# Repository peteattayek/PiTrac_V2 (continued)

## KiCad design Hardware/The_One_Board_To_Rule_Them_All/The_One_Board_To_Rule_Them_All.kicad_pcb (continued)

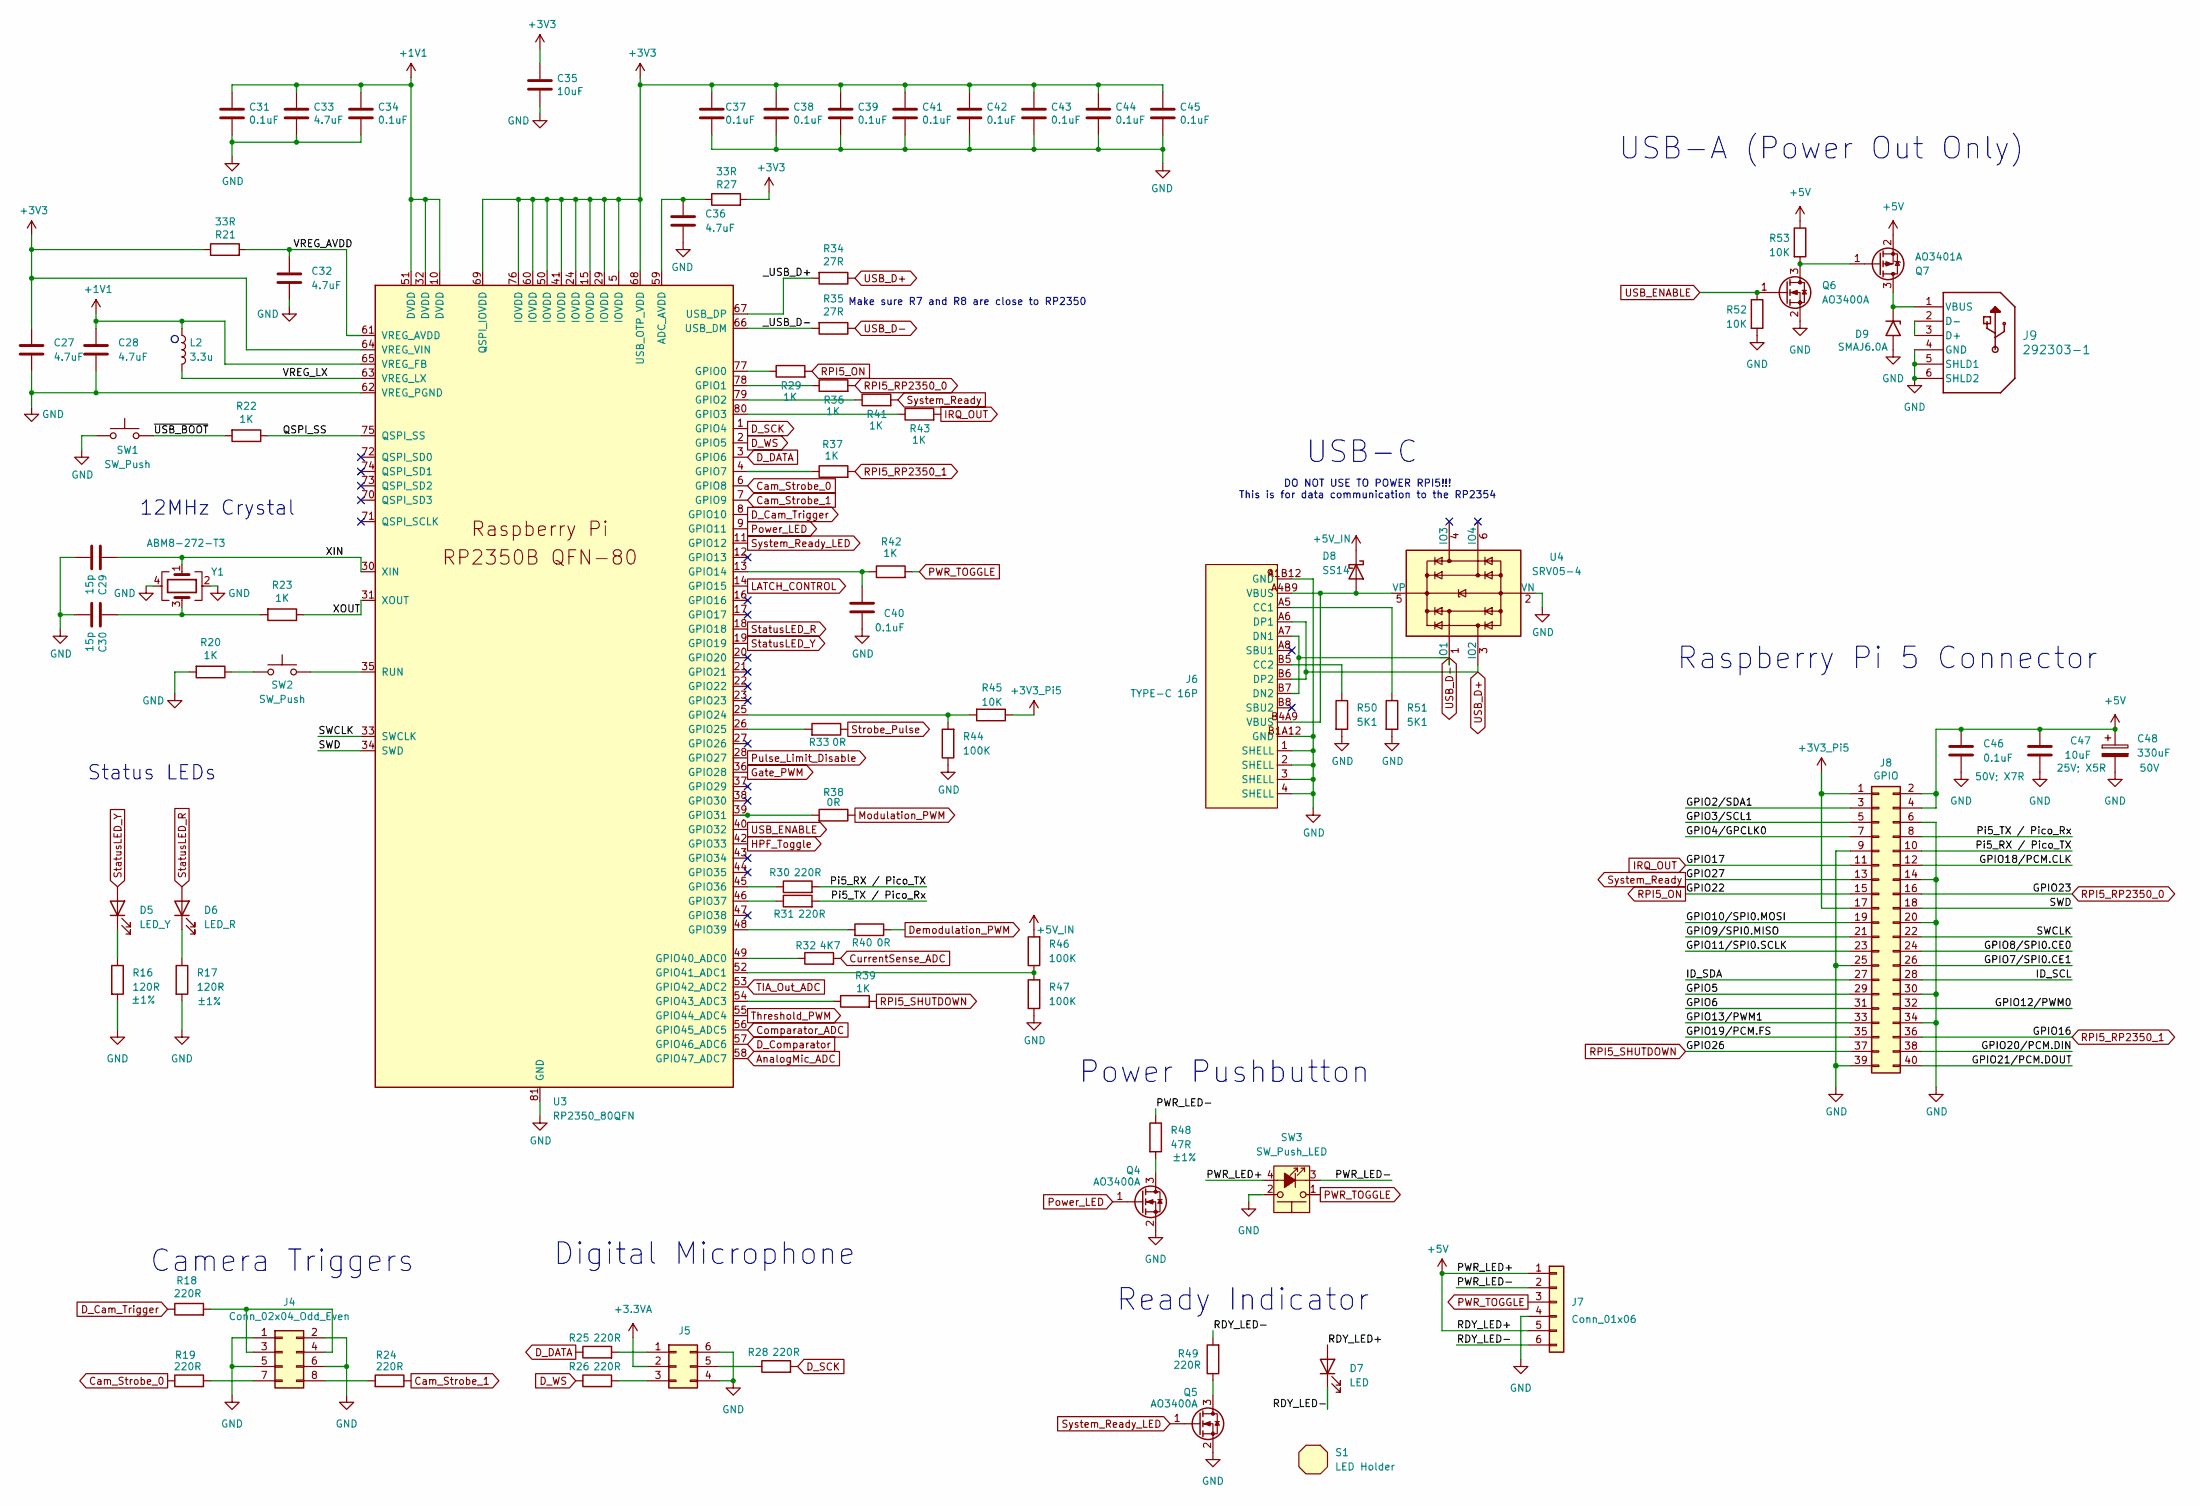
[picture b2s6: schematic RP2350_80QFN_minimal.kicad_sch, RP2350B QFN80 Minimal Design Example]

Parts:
C27, C28: 4.7uF; C_0402_1005Metric_small_pads; Ratings 10V; X5R; MPN CL05A475MP5NRNC; LCSC C23733
C29, C30: 15p; C_0402_1005Metric; Ratings C0G; MPN GRM1555C1H150JA01D; LCSC C1548
C31, C34, C37, C38, C39, C40, C41, C42, C43, C44, C45, C46: 0.1uF; C_0402_1005Metric; Ratings 50V; X7R; MPN CL05B104KB54PNC; LCSC C307331
C32, C33, C36: 4.7uF; C_0402_1005Metric; Ratings 10V; X5R; MPN CL05A475MP5NRNC; LCSC C23733
C35, C47: 10uF; C_0603_1608Metric; Ratings 25V; X5R; MPN CL10A106MA8NRNC; LCSC C96446
C48: 330uF; CAP_50TPV_10x10.5_RBY; Ratings 50V; MPN 50TPV330M10X10.5; LCSC C53120968
D5: LED_Y; LED_0603_1608Metric; MPN APT1608SYCK; LCSC C89811
D6: LED_R; LED_0603_1608Metric; MPN AA1608SURSK; LCSC C2286
D7: LED; MPN BL-BGE1V1
D8: SS14; D_SMA; MPN SS14; LCSC C2480
D9: SMAJ6.0A; D_SMA; MPN SMAJ6.0A; LCSC C19077525
J4: Conn_02x04_Odd_Even; PinHeader_2x04_P2.54mm_Vertical; MPN PH2-08-UA
J5: Conn_02x03_Counter_Clockwise; PinHeader_2x03_P2.54mm_Vertical; MPN PH2-06-UA
J6: TYPE-C 16P; USB-C-SMD_TYPE-C16PIN_C668624; MPN USB4105-GF-A; LCSC Part C668624
J7: Conn_01x06; PinHeader_1x06_P2.54mm_Vertical; MPN PH1-06-UA
J8: GPIO; PinSocket_2x20_P2.54mm_Vertical; MPN 16764
J9: 292303-1; CONN4_292303-1_TEC; MPN 292303-1
L2: 3.3u; L_pol_2016; MPN AOTA-B201610S3R3-101-T; LCSC C42411119
Q4, Q5: AO3400A; SOT-23; MPN AO3400A; LCSC C20917
Q6: AO3400A; SOT-23; MPN AO3400A; Digikey PN 785-1000-1-ND
Q7: AO3401A; SOT-23; MPN AO3401A; LCSC C15127
R16, R17: 120R; R_0402_1005Metric; Ratings ±1%; MPN RMCF0402FT120R; LCSC C25079
R18, R19, R24, R25, R26, R28, R30, R31, R49: 220R; R_0402_1005Metric; Ratings ±1%; MPN RMCF0402FT220R; LCSC C25091
R20, R22, R23, R29, R36, R37, R39, R41, R42, R43: 1K; R_0402_1005Metric; Ratings ±1%; MPN RMCF0402FT1K00; LCSC C11702
R21, R27: 33R; R_0402_1005Metric; Ratings ±1%; MPN RMCF0402FT33R0; LCSC C25105
R32: 4K7; R_1206_3216Metric; Ratings ±1% 1/4W; MPN RMCF1206FT4K70; LCSC C17936
R33, R38, R40: 0R; R_0805_2012Metric_Pad1.20x1.40mm_HandSolder; MPN RMCF0805ZT0R00; LCSC C17477
R34, R35: 27R; R_0603_1608Metric; Ratings ±1%; MPN RMCF0603FT27R0; LCSC C25190
R44, R46, R47: 100K; R_0402_1005Metric; Ratings ±1%; MPN RMCF0402FT100K; LCSC C25741
R45, R52, R53: 10K; R_0402_1005Metric; Ratings ±1%; MPN RMCF0402FT10K0; LCSC C25744
R48: 47R; R_0402_1005Metric; Ratings ±1%; MPN RMCF0402FT47R0; LCSC C25118
R50, R51: 5K1; R_0402_1005Metric; Ratings ±1%; MPN RMCF0402FT5K10; LCSC C25905
S1: LED Holder; MPN SSH-LXH501
SW1, SW2: SW_Push; SW_TS-1088_XNP; MPN TS-1088-AR02016; LCSC C720477
SW3: SW_Push_LED; MPN 481
U3: RP2350_80QFN; RP2350-QFN-80-1EP_10x10_P0.4mm_EP3.4x3.4mm_ThermalVias; MPN RP2354B; LCSC C39843328
U4: SRV05-4; SOT-23-6; MPN SRV05-4HTG-D; LCSC C7420376
Y1: ABM8-272-T3; Crystal_SMD_3225-4Pin_3.2x2.5mm; MPN ABM8-272-T3; LCSC C20625731

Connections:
+1V1: C28.1, C31.1, C33.1, C34.1, L2.1, U3.10 (DVDD), U3.32 (DVDD), U3.51 (DVDD), U3.65 (VREG_FB)
+3.3VA: J5.2; also elsewhere on the board
+3V3: C27.1, C35.1, C37.1, C38.1, C39.1, C41.1, C42.1, C43.1, C44.1, C45.1, R21.1, R27.2, U3.5 (IOVDD), U3.15 (IOVDD), U3.24 (IOVDD), U3.29 (IOVDD), U3.41 (IOVDD), U3.50 (IOVDD), U3.60 (IOVDD), U3.64 (VREG_VIN), U3.68 (USB_OTP_VDD), U3.69 (QSPI_IOVDD), U3.76 (IOVDD); also elsewhere on the board
+3V3_Pi5: J8.1, J8.17, R45.1
+5V: C46.2, C47.1, C48.1, D7.2 (A), J7.1, J7.5, J8.2, J8.4, Q7.2 (S), R53.1, SW3.4 (A); also elsewhere on the board
+5V_IN: D8.1 (K), R46.2; also elsewhere on the board
/MCU and Connectors/GPIO2/SDA1: J8.3
/MCU and Connectors/GPIO3/SCL1: J8.5
/MCU and Connectors/GPIO4/GPCLK0: J8.7
/MCU and Connectors/GPIO5: J8.29
/MCU and Connectors/GPIO6: J8.31
/MCU and Connectors/GPIO7/SPI0.CE1: J8.26
/MCU and Connectors/GPIO8/SPI0.CE0: J8.24
/MCU and Connectors/GPIO9/SPI0.MISO: J8.21
/MCU and Connectors/GPIO10/SPI0.MOSI: J8.19
/MCU and Connectors/GPIO11/SPI0.SCLK: J8.23
/MCU and Connectors/GPIO12/PWM0: J8.32
/MCU and Connectors/GPIO13/PWM1: J8.33
/MCU and Connectors/GPIO18/PCM.CLK: J8.12
/MCU and Connectors/GPIO19/PCM.FS: J8.35
/MCU and Connectors/GPIO20/PCM.DIN: J8.38
/MCU and Connectors/GPIO21/PCM.DOUT: J8.40
/MCU and Connectors/ID_SCL: J8.28
/MCU and Connectors/ID_SDA: J8.27
/MCU and Connectors/PWR_LED-: J7.2, R48.1, SW3.3 (K)
/MCU and Connectors/Pi5_RX / Pico_TX: J8.10, R30.2
/MCU and Connectors/Pi5_TX / Pico_Rx: J8.8, R31.2
/MCU and Connectors/QSPI_SS: R22.1, U3.75 (QSPI_SS)
/MCU and Connectors/RDY_LED-: D7.1 (K), J7.6, R49.2
/MCU and Connectors/SWCLK: J8.22, U3.33 (SWCLK)
/MCU and Connectors/SWD: J8.18, U3.34 (SWD)
/MCU and Connectors/VREG_AVDD: C32.1, R21.2, U3.61 (VREG_AVDD)
/MCU and Connectors/VREG_LX: L2.2, U3.63 (VREG_LX)
/MCU and Connectors/XIN: C29.1, U3.30 (XIN), Y1.1
/MCU and Connectors/XOUT: R23.1, U3.31 (XOUT)
/MCU and Connectors/_USB_D+: R34.2, U3.67 (USB_DP)
/MCU and Connectors/_USB_D-: R35.2, U3.66 (USB_DM)
/MCU and Connectors/~USB_BOOT: R22.2, SW1.2
AnalogMic_ADC: U3.58 (GPIO47_ADC7); also elsewhere on the board
Cam_Strobe_0: R19.1, U3.6 (GPIO8)
Cam_Strobe_1: R24.1, U3.7 (GPIO9)
Comparator_ADC: U3.56 (GPIO45_ADC5); also elsewhere on the board
CurrentSense_ADC: R32.2; also elsewhere on the board
D_Cam_Trigger: R18.1, U3.8 (GPIO10)
D_Comparator: U3.57 (GPIO46_ADC6); also elsewhere on the board
D_DATA: R25.1, U3.3 (GPIO6)
D_SCK: R28.2, U3.1 (GPIO4)
D_WS: R26.1, U3.2 (GPIO5)
Demodulation_PWM: R40.1; also elsewhere on the board
GND: C27.2, C28.2, C29.2, C30.2, C31.2, C32.2, C33.2, C34.2, C35.2, C36.2, C37.2, C38.2, C39.2, C40.1, C41.2, C42.2, C43.2, C44.2, C45.2, C46.1, C47.2, C48.2, D9.2 (A2), J4.1, J4.2, J4.5, J4.6, J5.4, J5.6, J6.1 (SHELL), J6.2 (SHELL), J6.3 (SHELL), J6.4 (SHELL), J6.A1B12 (GND), J6.B1A12 (GND), J7.4, J8.6, J8.9, J8.14, J8.20, J8.25, J8.30, J8.34, J8.39, J9.4 (GND), J9.5 (SHLD1), J9.6 (SHLD2), Q4.2 (S), Q5.2 (S), Q6.2 (S), R16.2, R17.2, R20.2, R44.1, R47.1, R50.2, R51.2, R52.2, SW1.1, SW3.2, U3.62 (VREG_PGND), U3.81 (GND), U4.2 (VN), Y1.2, Y1.4; also elsewhere on the board
Gate_PWM: U3.36 (GPIO28); also elsewhere on the board
HPF_Toggle: U3.42 (GPIO33); also elsewhere on the board
IRQ_OUT: J8.11, R43.2
LATCH_CONTROL: U3.14 (GPIO15); also elsewhere on the board
Modulation_PWM: R38.1; also elsewhere on the board
unnamed: C30.1, R23.2, Y1.3
unnamed: D5.1 (K), R16.1
unnamed: D6.1 (K), R17.1
unnamed: D8.2 (A), J6.A4B9 (VBUS), J6.B4A9 (VBUS), U4.5 (VP)
unnamed: D9.1 (A1), J9.1 (VBUS), Q7.3 (D)
unnamed: J4.3, J4.4, R18.2
unnamed: J4.7, R19.2
unnamed: J4.8, R24.2
unnamed: J5.1, R25.2
unnamed: J5.3, R26.2
unnamed: J5.5, R28.1
unnamed: J6.A5 (CC1), R51.1
unnamed: J6.B5 (CC2), R50.1
unnamed: J9.2 (D-), J9.3 (D+)
unnamed: Q4.3 (D), R48.2
unnamed: Q5.3 (D), R49.1
unnamed: Q6.3 (D), Q7.1 (G), R53.2
unnamed: R20.1, SW2.1
unnamed: C36.1, R27.1, U3.59 (ADC_AVDD)
unnamed: R29.1, U3.77 (GPIO0)
unnamed: R36.1, U3.78 (GPIO1)
unnamed: R41.1, U3.79 (GPIO2)
unnamed: R43.1, U3.80 (GPIO3)
unnamed: R37.1, U3.4 (GPIO7)
unnamed: C40.2, R42.1, U3.13 (GPIO14)
unnamed: R44.2, R45.2, U3.25 (GPIO24)
unnamed: R33.2, U3.26 (GPIO25)
unnamed: R38.2, U3.39 (GPIO31)
unnamed: R30.1, U3.45 (GPIO36)
unnamed: R31.1, U3.46 (GPIO37)
unnamed: R40.2, U3.48 (GPIO39)
unnamed: R32.1, U3.49 (GPIO40_ADC0)
unnamed: R46.1, R47.2, U3.52 (GPIO41_ADC1)
unnamed: R39.1, U3.54 (GPIO43_ADC3)
unnamed: SW2.2, U3.35 (RUN)
PWR_TOGGLE: J7.3, R42.2, SW3.1
Power_LED: Q4.1 (G), U3.9 (GPIO11)
Pulse_Limit_Disable: U3.28 (GPIO27); also elsewhere on the board
RPI5_ON: J8.15, R29.2
RPI5_RP2350_0: J8.16, R36.2
RPI5_RP2350_1: J8.36, R37.2
RPI5_SHUTDOWN: J8.37, R39.2
StatusLED_R: D6.2 (A), U3.18 (GPIO18)
StatusLED_Y: D5.2 (A), U3.19 (GPIO19)
Strobe_Pulse: R33.1; also elsewhere on the board
System_Ready: J8.13, R41.2
System_Ready_LED: Q5.1 (G), U3.11 (GPIO12)
TIA_Out_ADC: U3.53 (GPIO42_ADC2); also elsewhere on the board
Threshold_PWM: U3.55 (GPIO44_ADC4); also elsewhere on the board
USB_D+: J6.A6 (DP1), J6.B6 (DP2), R34.1, U4.3 (IO2)
USB_D-: J6.A7 (DN1), J6.B7 (DN2), R35.1, U4.1 (IO1)
USB_ENABLE: Q6.1 (G), R52.1, U3.40 (GPIO32)

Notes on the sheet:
12MHz Crystal
USB-C
DO NOT USE TO POWER RPI5!!! This is for data communication to the RP2354
Ready Indicator
Status LEDs
Camera Triggers
Digital Microphone
USB-A (Power Out Only)
Power Pushbutton
Raspberry Pi 5 Connector
Make sure R7 and R8 are close to RP2350

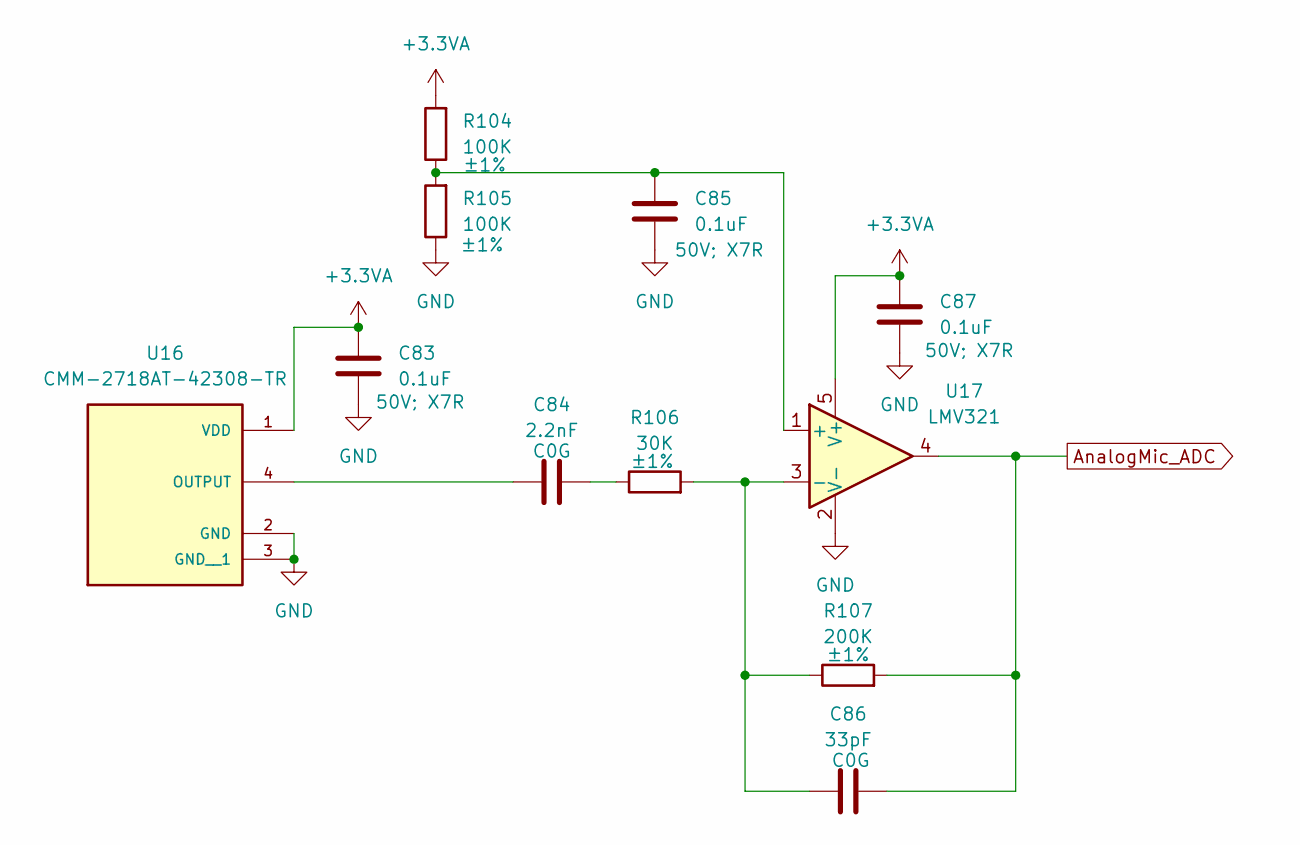
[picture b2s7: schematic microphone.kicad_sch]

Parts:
C83, C85, C87: 0.1uF; C_0402_1005Metric; Ratings 50V; X7R; MPN CL05B104KB54PNC; LCSC C307331
C84: 2.2nF; C_0805_2012Metric; Ratings C0G; MPN CL21C222JBFNNNE; LCSC C28260
C86: 33pF; C_0603_1608Metric; Ratings C0G; MPN CL10C330JB8NNNC; LCSC C1663
R104, R105: 100K; R_0402_1005Metric; Ratings ±1%; MPN RMCF0402FT100K; LCSC C25741
R106: 30K; R_0603_1608Metric; Ratings ±1%; MPN RMCF0603FT30K0; LCSC C22984
R107: 200K; R_0402_1005Metric; Ratings ±1%; MPN RMCF0402FT200K; LCSC C25764
U16: CMM-2718AT-42308-TR; XDCR_CMM-2718AT-42308-TR; MPN CMM-2718AT-42308-TR; LCSC C481300
U17: LMV321; SOT-23-5; MPN LMV321IDBVR; LCSC C7972

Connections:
+3.3VA: C83.2, C87.2, R104.2, U16.1 (VDD), U17.5 (V+); also elsewhere on the board
AnalogMic_ADC: C86.2, R107.2, U17.4; also elsewhere on the board
GND: C83.1, C85.1, C87.1, R105.1, U16.2 (GND), U16.3 (GND__1), U17.2 (V-); also elsewhere on the board
unnamed: C84.2, R106.1
unnamed: C84.1, U16.4 (OUTPUT)
unnamed: C85.2, R104.1, R105.2, U17.1 (+)
unnamed: C86.1, R106.2, R107.1, U17.3 (-)

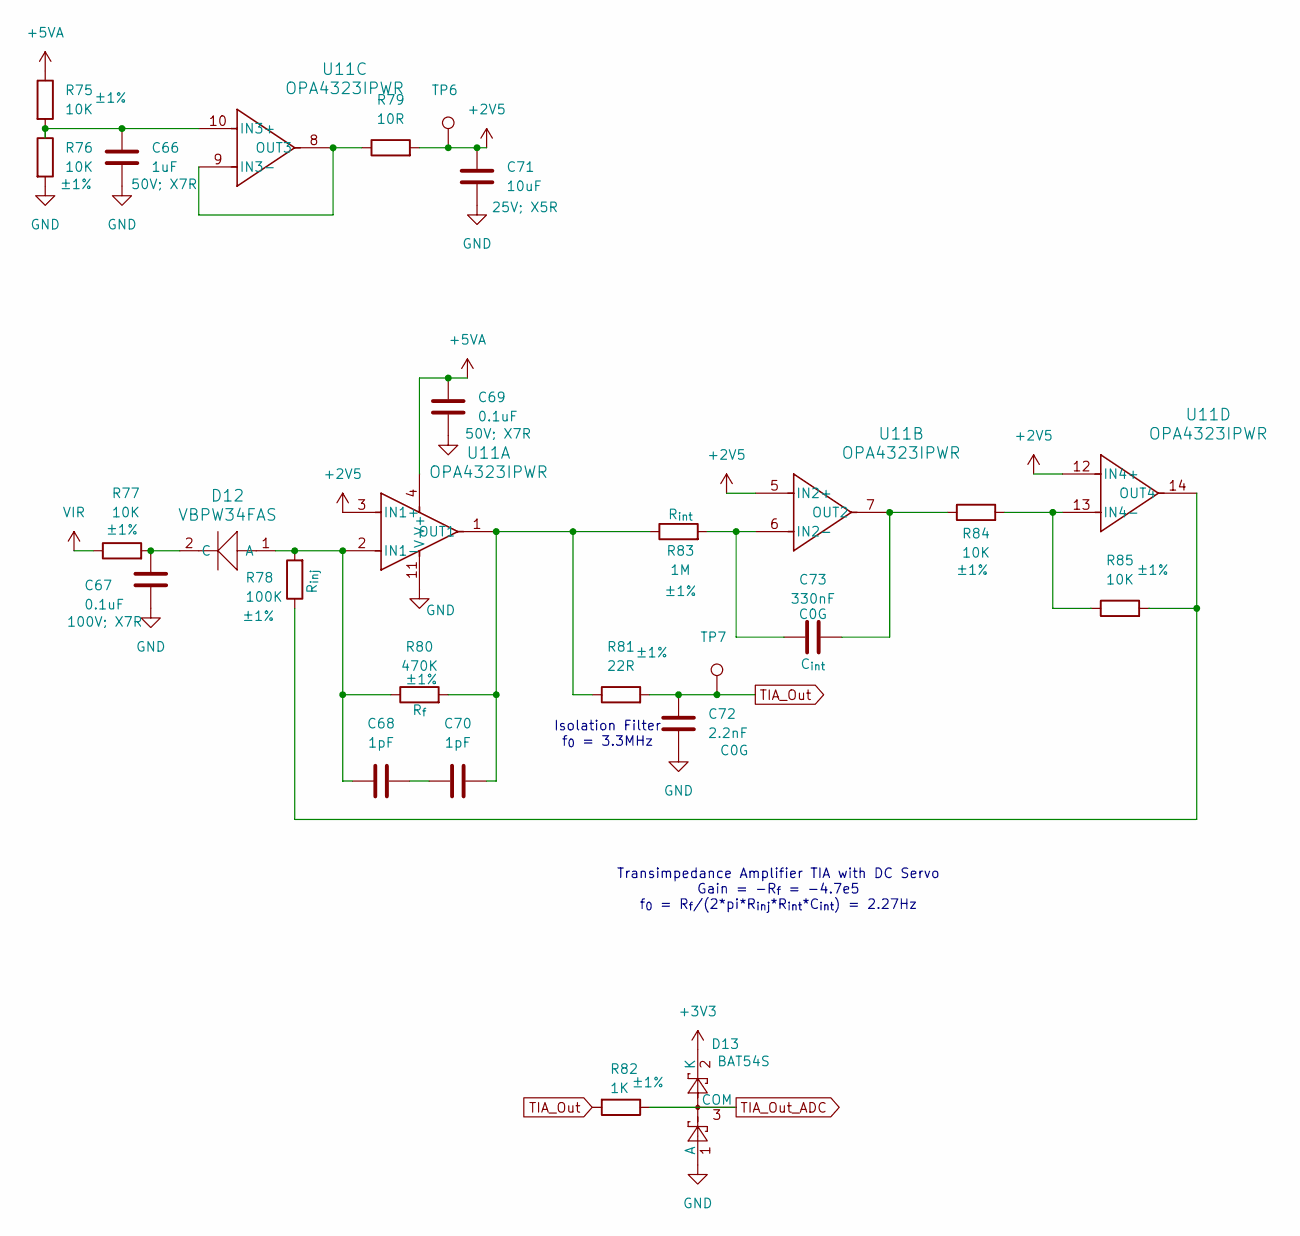
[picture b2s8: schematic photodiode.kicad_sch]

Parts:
C66: 1uF; C_0805_2012Metric; Ratings 50V; X7R; MPN CL21B105KBFNNNE; LCSC C28323
C67: 0.1uF; C_0805_2012Metric; Ratings 100V; X7R; MPN CL21B104KCFNNNE; LCSC C28233
C68, C70: 1pF; C_0402_1005Metric; Ratings C0G; MPN GRM1555C1H1R0BA01D; LCSC C1550
C69: 0.1uF; C_0402_1005Metric; Ratings 50V; X7R; MPN CL05B104KB54PNC; LCSC C307331
C71: 10uF; C_0603_1608Metric; Ratings 25V; X5R; MPN CL10A106MA8NRNC; LCSC C96446
C72: 2.2nF; C_0805_2012Metric; Ratings C0G; MPN CL21C222JBFNNNE; LCSC C28260
C73: 330nF; C_1206_3216Metric; Ratings C0G; MPN GRM31C5C1E334JE01L; LCSC C3837965
D12: VBPW34FAS; CR_W34FAS_VIS; MPN VBPW34FAS; LCSC C413453
D13: BAT54S; SOT-23; MPN BAT54SLT1G; LCSC C7420333
R75, R76, R77, R84, R85: 10K; R_0402_1005Metric; Ratings ±1%; MPN RMCF0402FT10K0; LCSC C25744
R78: 100K; R_0402_1005Metric; Ratings ±1%; MPN RMCF0402FT100K; LCSC C25741
R79: 10R; R_0402_1005Metric; Ratings ±1%; MPN RMCF0402FT10R0; LCSC C25077
R80: 470K; R_0603_1608Metric; Ratings ±1%; MPN RMCF0603FT470K; LCSC C23178
R81: 22R; R_0402_1005Metric; Ratings ±1%; MPN RMCF0402FT22R0; LCSC C25092
R82: 1K; R_0402_1005Metric; Ratings ±1%; MPN RMCF0402FT1K00; LCSC C11702
R83: 1M; R_0603_1608Metric; Ratings ±1%; MPN RMCF0603FT1M00; LCSC C22935
TP6, TP7: TestPoint; TestPoint_THTPad_D1.0mm_Drill0.5mm
U11: OPA4323IPWR; PW0014A-IPC_A; MPN OPA4323IPWR; LCSC C22419728

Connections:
+2V5: C71.1, R79.2, TP6.1 (1_1), U11.3 (IN1+), U11.5 (IN2+), U11.12 (IN4+); also elsewhere on the board
+3V3: D13.2 (K); also elsewhere on the board
+5VA: C69.1, R75.1, U11.4 (V+); also elsewhere on the board
GND: C66.2, C67.2, C69.2, C71.2, C72.2, D13.1 (A), R76.2, U11.11 (V-); also elsewhere on the board
unnamed: C68.1, C70.2
unnamed: C68.2, D12.1 (A), R78.2, R80.1, U11.2 (IN1-)
unnamed: C67.1, D12.2 (C), R77.2
unnamed: C70.1, R80.2, R81.1, R83.1, U11.1 (OUT1)
unnamed: C73.1, R83.2, U11.6 (IN2-)
unnamed: C73.2, R84.1, U11.7 (OUT2)
unnamed: C66.1, R75.2, R76.1, U11.10 (IN3+)
unnamed: R79.1, U11.8 (OUT3), U11.9 (IN3-)
unnamed: R84.2, R85.1, U11.13 (IN4-)
unnamed: R78.1, R85.2, U11.14 (OUT4)
TIA_Out: C72.1, R81.2, R82.2, TP7.1 (1_1); also elsewhere on the board
TIA_Out_ADC: D13.3 (COM), R82.1; also elsewhere on the board
VIR: R77.1; also elsewhere on the board

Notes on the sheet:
Isolation Filter f_{0} = 3.3MHz
Transimpedance Amplifier TIA with DC Servo Gain = -R_{f} = -4.7e5 f_{0} = R_{f}/(2*pi*R_{inj}*R_{int}*C_{int}) = 2.27Hz

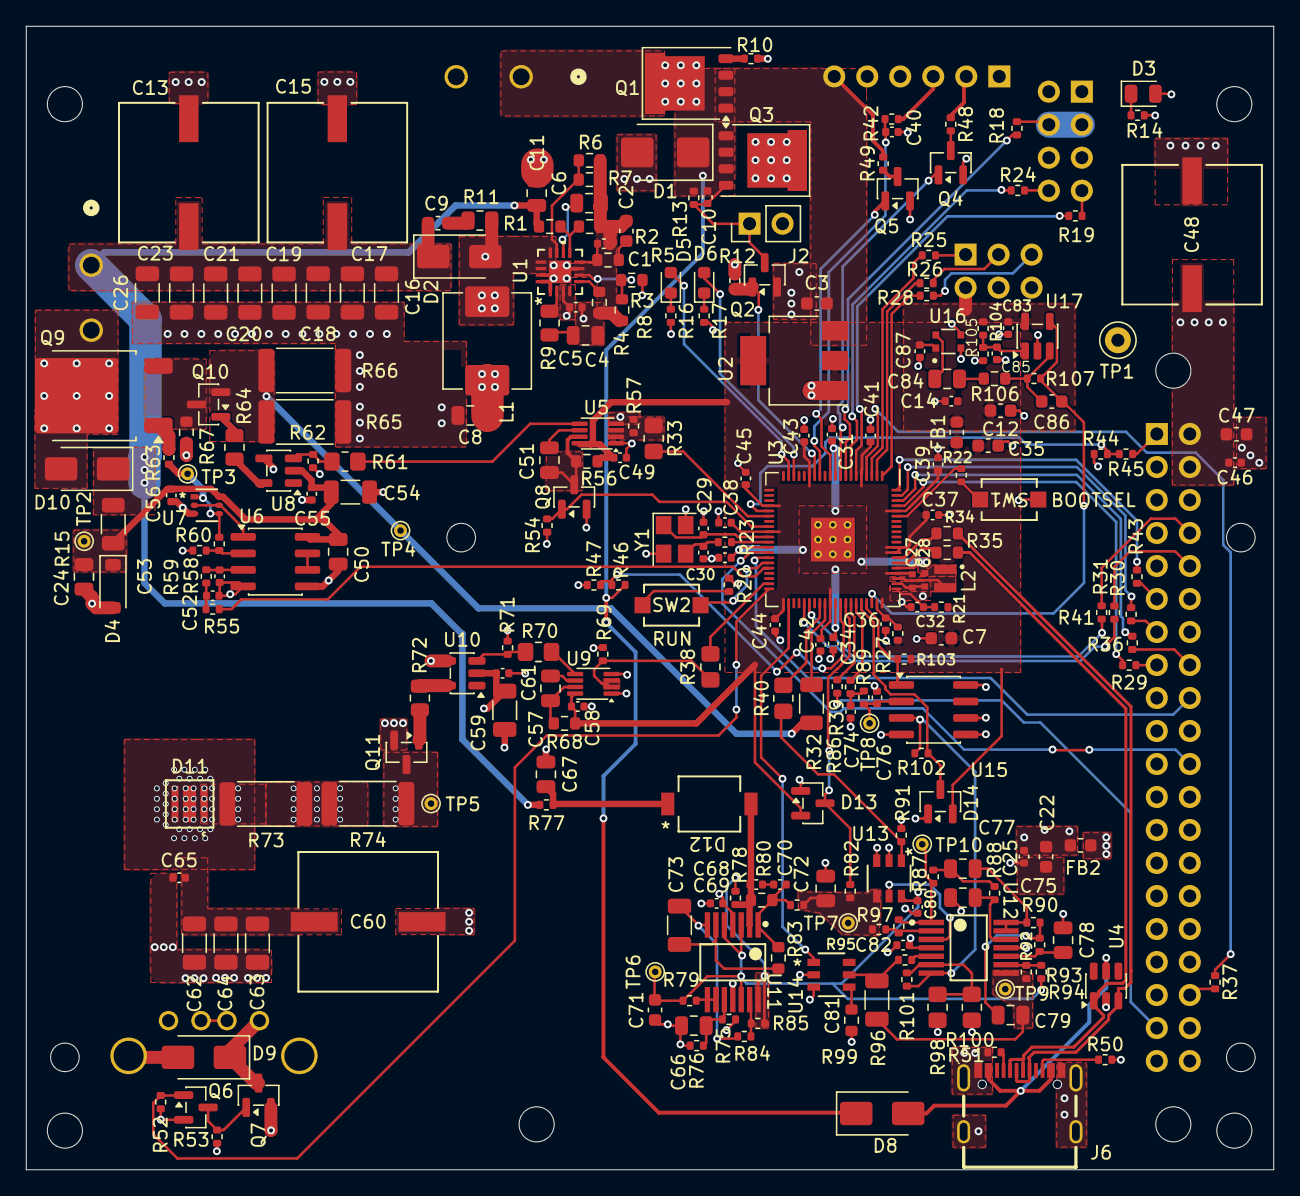
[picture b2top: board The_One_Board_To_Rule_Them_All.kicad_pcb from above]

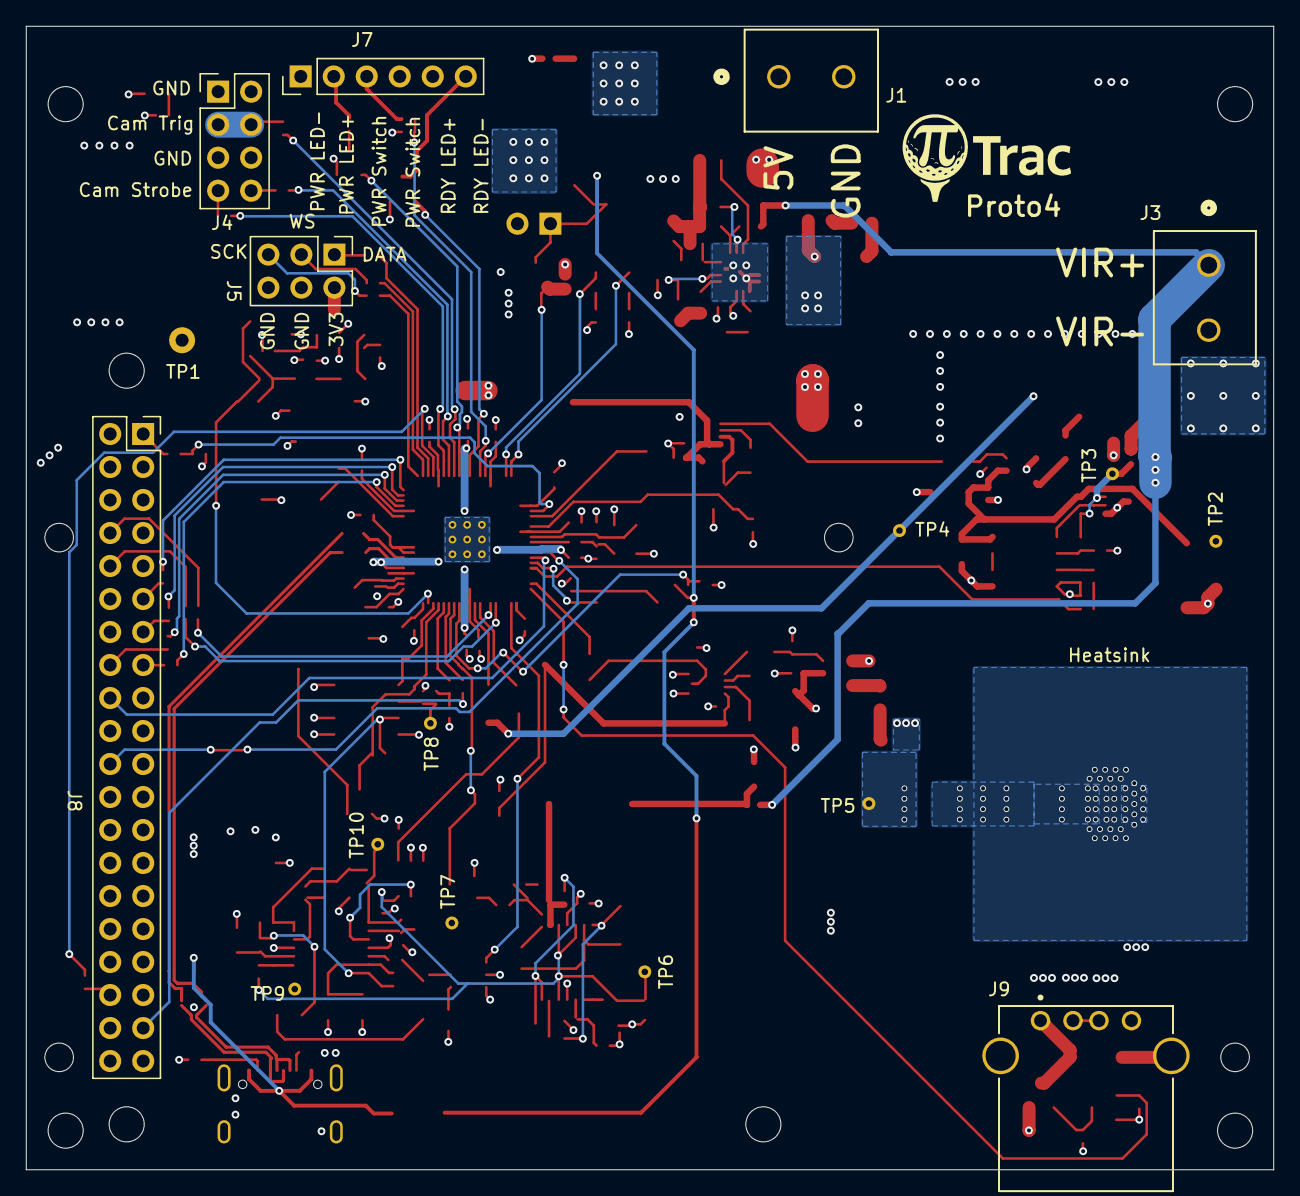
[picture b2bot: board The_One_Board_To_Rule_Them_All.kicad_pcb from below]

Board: 4 copper layers, 96.0 x 88.0 mm, 273 parts (11 on the bottom side), 165 nets.

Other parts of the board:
MH1, MH2, MH4: MountingHole_2.7mm_M2.5

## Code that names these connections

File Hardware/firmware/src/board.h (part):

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// HARDWARE FACTS THAT CONSTRAIN THE FIRMWARE -- do not "simplify" these away
// ===========================================================================
//
// 1. PIN_PWR_TOGGLE (GPIO14) has NO EXTERNAL PULL-UP. The internal pull-up is
//    load-bearing. R42 1K + C40 100 nF give ~100 us of hardware filtering only.
//
// 2. PIN_PULSE_LIMIT_DIS (GPIO27) DEFEATS THE STROBE HARDWARE WATCHDOG.
//    It is written 0 in exactly one place (safe_state()) and nowhere else.
//    There must be no CLI path and no config flag that raises it until the
//    strobe phase is fully characterised. A stuck-high strobe with the
//    watchdog defeated destroys the LED bank and possibly Q9.
//
// 3. The +5V latch (GPIO15) IS THE PI 5's POWER SWITCH. Raising it with a Pi
//    seated and no orderly shutdown corrupts the SD card. Raising it on
//    USB-only power browns out everything. Guarded by V5_MIN_FOR_LATCH at latch
//    time and V5_MIN_SUSTAINED continuously thereafter.
//
// 4. D_COMPARATOR (GPIO46) has an EXTERNAL 10K pull-up (R103). Do not enable
//    an internal pull.
//
// 5. The beam LED is NOT driven directly by the MCU. PIN_MOD_PWM feeds a
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//
// 8. RP2350 erratum E9 (check your die revision): a GPIO input with the
//    INTERNAL PULL-DOWN enabled, driven from a high-impedance source, can latch
//    around 2.2 V instead of pulling to 0. PIN_CAM_STROBE_0/1 and PIN_RPI5_ON
//    are exactly that configuration when the connectors are unpopulated.
//    Never use them as a safety interlock without software confirmation.

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// ===========================================================================

// --- Raspberry Pi 5 interface (J8 40-pin header) ---------------------------
#define PIN_RPI5_ON          0   // in  : Pi userspace up      (J8.15 <- Pi GPIO22, R29 1K)
#define PIN_HANDSHAKE_0      1   // bidir spare                (J8.16 <-> Pi GPIO23, R36 1K)
#define PIN_SYSTEM_READY     2   // out : armed mirror         (J8.13 -> Pi GPIO27, R41 1K)
#define PIN_IRQ_OUT          3   // out : capture-complete     (J8.11 -> Pi GPIO17, R43 1K)
#define PIN_HANDSHAKE_1      7   // bidir spare                (J8.36 <-> Pi GPIO16, R37 1K)
#define PIN_PI_3V3_SENSE    24   // in  : Pi 3V3 present. R45 10K / R44 100K divider
                                 //       -> 3.3 V * 0.909 = 3.0 V when the Pi is powered.
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                                 //       (measured 2026-11-09, BENCH_P8_PI.md 8.1/8.2): this
                                 //       shows power, not "the Pi is down". RPI5_ON is the
                                 //       only down indicator that works (power_pi_is_down()).
#define PIN_RPI5_SHUTDOWN   43   // out : shutdown request     (J8.37 -> Pi GPIO26, R39 1K)

// --- External I2S microphone (J5) ------------------------------------------
#define PIN_I2S_SCK          4   // out (PIO1)  J5.5, R28 220R
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#define PIN_I2S_DATA         6   // in  (PIO1)  J5.1, R25 220R

// --- Cameras (J4) -----------------------------------------------------------
#define PIN_CAM_STROBE_0     8   // in  : cam0 exposure active (J4.7, R19 220R)
#define PIN_CAM_STROBE_1     9   // in  : cam1 exposure active (J4.8, R24 220R)
#define PIN_CAM_TRIGGER     10   // out : both cameras         (J4.3/4, R18 220R)

// --- Panel (J7) and on-board indicators ------------------------------------
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#define PIN_LED_YELLOW      19   // out : on-board D5, 120R, ACTIVE HIGH, always-on +3V3

// --- Power control ----------------------------------------------------------
#define PIN_PWR_TOGGLE      14   // in  : panel button, ACTIVE LOW, INTERNAL PULL-UP REQUIRED
#define PIN_LATCH_CONTROL   15   // out : high = +5V rail on. Q2 gate; R12 10K pulldown.

// --- Strobe -----------------------------------------------------------------
#define PIN_STROBE_PULSE    25   // out (PIO0) : hardware-clamped pulse gate. R57 1K pulldown.
#define PIN_PULSE_LIMIT_DIS 27   // out : DANGER -- defeats the strobe watchdog. TEST ONLY.
#define PIN_GATE_PWM        28   // out (PWM 6A) : strobe current setpoint DAC
                                 //   *** SHARES SLICE 6A WITH PIN_READY_LED (GPIO12).
                                 //   *** Resolved in firmware 2026-10-02: GPIO12 is SIO
                                 //   *** on/off and strobe.c owns slice 6. See the map.

// --- Optical chain ----------------------------------------------------------
#define PIN_MOD_PWM         31   // out (PWM 7B) : beam carrier. R69 1K pulldown.
                                 //   *** shares slice 7B with PIN_LATCH_CONTROL (GPIO15).
                                 //   *** GPIO15 MUST STAY SIO. See the PWM SLICE MAP below.
#define PIN_HPF_TOGGLE      33   // out : U14 TMUX1219 SEL. 0 = TRACK, 1 = HOLD -- see below.
#define PIN_DEMOD_PWM       39   // out (PWM 11B): demod clock, phase-locked to slice 7
#define PIN_THRESHOLD_PWM   44   // out (PWM 10A): comparator threshold DAC (also ADC4 -- never sample)
#define PIN_D_COMPARATOR    46   // in  : ball-detect comparator. EXTERNAL 10K pull-up (R103).

// --- U14 gated HPF: which SEL level selects which path -----------------------
//
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// TMUX1219 truth table (TI datasheet): SEL = 0 -> S1 to D, SEL = 1 -> S2 to D.
// The unselected source goes high-impedance. Therefore on THIS board:
//
//        GPIO33 = 0  ->  S1  ->  R96/GND  ->  TRACK
//        GPIO33 = 1  ->  S2  ->  open     ->  HOLD
//
// **The netlist could not tell us this** -- it encodes only the pin name "SEL" --
// and BENCH_P3_DETECT.md's original assumption that `gpio 33 1` = TRACK was
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// reported INVERTED relative to the old constant, and the datasheet truth table
// says the same thing.
//
// Nothing else in the firmware may compare against PIN_HPF_TOGGLE's raw level.
#define HPF_SEL_TRACK        0    // level that selects S1 (the 2M/GND leg)

// C81, the hold capacitor. Used to turn the measured HOLD drift rate into a
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#define HPF_SEL_HOLD         (!HPF_SEL_TRACK)

// --- Misc -------------------------------------------------------------------
#define PIN_USB_ENABLE      32   // out : USB-A accessory VBUS switch (Q6 -> Q7)
#define PIN_UART_TX         36   // out : UART1 -> Pi RXD  (J8.10, R30 220R)
#define PIN_UART_RX         37   // in  : UART1 <- Pi TXD  (J8.8,  R31 220R)
                                 // Both connected to UART1 only while a Pi is up
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//     gpio < 32 :  slice = (gpio >> 1) & 7          channel = gpio & 1
//     gpio >= 32:  slice = 8 + ((gpio >> 1) & 3)    channel = gpio & 1
//
// Getting this wrong is easy and the earlier comments in this file did (GPIO28
// was documented as "2A", GPIO31 as "3B", GPIO39 as "7B" -- all wrong).
//
//   GPIO11  PWR_BTN_LED       slice  5B    panel, PWM, active
//   GPIO12  READY_LED         slice  6A    SIO ONLY (on/off) since 2026-10-02
//   GPIO15  LATCH_CONTROL     slice  7B    SIO ONLY
//   GPIO27  PULSE_LIMIT_DIS   slice  5B    SIO ONLY
//   GPIO28  GATE_PWM          slice  6A    strobe DAC, PWM, owned by strobe.c
//   GPIO31  MOD_PWM           slice  7B    beam carrier, PWM, active
//   GPIO39  DEMOD_PWM         slice 11B    demod clock, PWM, active
//   GPIO44  THRESHOLD_PWM     slice 10A    comparator DAC, Phase 3
//
// THREE PAIRS COLLIDE, and in every case it is the SAME CHANNEL, not merely the
// same slice. That distinction is the whole problem:
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// channel bit (gpio&1) is unchanged. 12/28, 15/31, 11/27 are all exactly 16 apart.
// **Design rule for the next board spin: never put two PWM functions on GPIOs
// 16 apart.** Note slice 6 channel B (GPIO13/GPIO29) is unassigned -- had the
// ready LED been routed to GPIO13, it and GPIO28 would have coexisted perfectly.
//
// 1. GPIO12 READY_LED  vs GPIO28 GATE_PWM   -- slice 6A. RESOLVED IN FIRMWARE
//    2026-10-02 (ARCHITECTURE.md A7). Whichever pin was configured second used to
//    take over both, so LED brightness could have become the strobe current
//    setpoint. The ready LED now gives up the PWM block: panel.c drives it as SIO
//    on/off, and strobe.c owns slice 6 and refuses to raise the gate if GPIO12 is
//    ever found on GPIO_FUNC_PWM again. Never put GPIO12 back on PWM.
//
// 2. GPIO15 LATCH_CONTROL vs GPIO31 MOD_PWM -- slice 7B. Safe ONLY because GPIO15
//    stays SIO. If GPIO15 were ever set to GPIO_FUNC_PWM it would switch the +5V
//    rail -- the Pi's power -- at the beam carrier frequency and duty. NEVER put
//    GPIO15 on PWM.
//
// 3. GPIO11 PWR_BTN_LED vs GPIO27 PULSE_LIMIT_DIS -- slice 5B. Safe ONLY because
//    GPIO27 stays SIO (see hard rule 2 above). If GPIO27 were ever set to
//    GPIO_FUNC_PWM it would toggle the strobe hardware watchdog defeat line at the
//    panel LED's ~1 kHz. NEVER put GPIO27 on PWM.
//
// beam.c and panel.c both resolve slices at runtime via pwm_gpio_to_slice_num(),
// so the CODE has always been correct. It was the documentation that was wrong.
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#define ADC_CH_CURRENT       0   // GPIO40 : strobe current sense, 135 mV/A (R65||R66 = 0.135R)
#define ADC_CH_5VIN          1   // GPIO41 : +5V_IN / 2 (R46 100K / R47 100K)
#define ADC_CH_TIA           2   // GPIO42 : raw TIA carrier (R82 1K + D13 BAT54S clamp)
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
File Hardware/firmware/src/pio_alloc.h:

// SPDX-License-Identifier: GPL-3.0-or-later
// Copyright (C) 2026 PiTrac contributors
// pio_alloc.h -- which PIO block owns what, and why it is not a free choice.
//
// RP2350 gives each PIO block ONE `GPIOBASE` register, and it holds only 0 or
// 16 (PIO_GPIOBASE_BITS = 0x10). So a block sees a 32-pin window: GPIO 0-31 or
// GPIO 16-47, never a mix. Every pin field in that block -- in/out/set/sideset
// bases and `jmp pin` -- lives inside that window.
//
// This project's PIO pins do not fit in one window:
//
//   GPIO 4/5/6    I2S mic          Phase 5   base 0 only
//   GPIO 8/9      Cam_Strobe_0/1   Phase 7   base 0 only
//   GPIO 10       Cam_Trigger      Phase 7   base 0 only
//   GPIO 25       Strobe_Pulse     Phase 6   either
//   GPIO 46       D_Comparator     Phase 3   base 16 only
//
// So the detector CANNOT share a block with the cameras or the mic. That is a
// hardware partition, not a preference -- an allocation that violates it does
// not merely perform badly, it fails to configure. The SDK enforces it:
// pio_sm_set_config() returns PICO_ERROR_BAD_ALIGNMENT if a config references
// pins 0-15 on a base-16 block or pins 32-47 on a base-0 block.
//
// ORDERING CONSTRAINT: pio_set_gpio_base() REFUSES once any program has been
// loaded into that block (it checks the block's used-instruction-space mask).
// Hence one pio_alloc_init() called from main() before every other init that
// might touch PIO. Getting this wrong is silent at compile time and fatal at
// run time, which is exactly why the map is a declared artifact here rather
// than something each module discovers for itself.
//
// We have 8 free state machines across three blocks, so spending a whole block
// on one detector costs nothing. Do not "optimise" this by consolidating.

#ifndef PITRAC_PIO_ALLOC_H
#define PITRAC_PIO_ALLOC_H

#include "hardware/pio.h"

// --- Block 0: base 0. The strobe (and the microphone, if it is ever built). -
// Instruction memory: strobe_burst.pio (12) at offset 20, strobe_gate.pio (1)
// at 19, directly below it (strobe.c). 19 free.
#define PIO_BLK_LOW       pio0
#define PIO_BASE_LOW      0u
#define PIO_SM_STROBE     0u      // Phase 6, GPIO25
// The camera's FIRE: a flag in THIS block, raised from the camera's block with
// `irq prev set 4` (RP2350), waited on by strobe_gate.pio. Flags 4-7 never
// reach a system interrupt, so nothing else sees it.
#define PIO_IRQ_CAM_FIRE  4u

// The I2S mic (Phase 5, GPIO4/5/6, optional, deferred) was planned for PIO1 SM0.
// The camera now fills PIO1, so the mic belongs here, in PIO0's 19 free
// instructions. Nothing is written for it.
#define PIO_BLK_MIC       pio0
#define PIO_BASE_MIC      0u
#define PIO_SM_I2S        1u      // Phase 5, GPIO4/5/6 -- planned, no firmware

// --- Block 1: base 0. The camera handshake (Phase 7, ARCHITECTURE.md A3). ---
// cam_handshake.pio is 29 instructions, so it has the block to itself. Its
// FIRE reaches the strobe engine through `irq prev`, which names the block
// numbered one below: PIO1 -> PIO0. pio_alloc_init() checks that relation.
#define PIO_BLK_CAMERA    pio1
#define PIO_BASE_CAMERA   0u
#define PIO_SM_CAMERA     0u      // GPIO8/9 in, GPIO10 out

// --- Block 2: base 16. Everything in the high bank. -------------------------
// GPIO46 forces this. Any future PIO use of GPIO32-47 belongs here too.
#define PIO_BLK_HIGH      pio2
#define PIO_BASE_HIGH     16u
#define PIO_SM_DETECT     0u      // Phase 3/4, GPIO46

// Sets both GPIO bases. MUST be called before any pio_add_program() anywhere.
// Panics if either call fails -- a wrong base is not a condition to limp along
// with, because every pin field configured afterwards would be silently wrong.
void pio_alloc_init(void);

#endif // PITRAC_PIO_ALLOC_H
